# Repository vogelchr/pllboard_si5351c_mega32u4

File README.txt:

Si5351C PLL + ATmega32U4 PLL / OCXO-Control / Clock Generator

A PCB to provide a Si5351C clock generator IC with power via USB
and also have a ATmega32U4 control it.

The PLL chip can be provided two clocks:

 (1) standalone XTAL for Si5351C
      -> populate XT2

 (2a) external reference input (X8)
     (top right SMA connector when looking at top layer of PCB)

     -> Populate R18 (termination for SMA X8)
     -> Populate R27 (connects X8 with J3, Pin7)
     -> Populate R21, R22 (voltage divider to match Si5351C clkin voltage)

 (2b) quartz (TCXO, OCXO) oscillator connected to J3

     -> Populate R21, R22 (voltage divider to match Si5351C clkin voltage)
     -> A MCP47x6 DAC can be populated to provide a control voltage

If the clock (2a/2b) should be disciplined, this can be achieved
by having the ATmega32U4 determine the clock phase.

 (1) have a 1PPS input on the reference input (X8)

     -> Populate R17, R18 (termination, series resistor) for the
        atmega32u4 comparator input

     Then have the Si5351C output a suitable frequency to the atmega32u4
     on clock output 3, and...

     -> pouplate R25 to feed the external timer clock input T0,
        which has a maximum frequency of clkIO/2

          or

     -> populate R26, R20 and feed this frequency to the atmega32u4
        as the system clock. in this case, the otp memory of the
        Si5351C will have to be programmed so that it starts up
        with the clk3 active, and care must be taken not to turn
        off this clock, or the atmega32u4 will stop operating

     This way the ATmega32U4 can measure the clock phase of the 1PPS.

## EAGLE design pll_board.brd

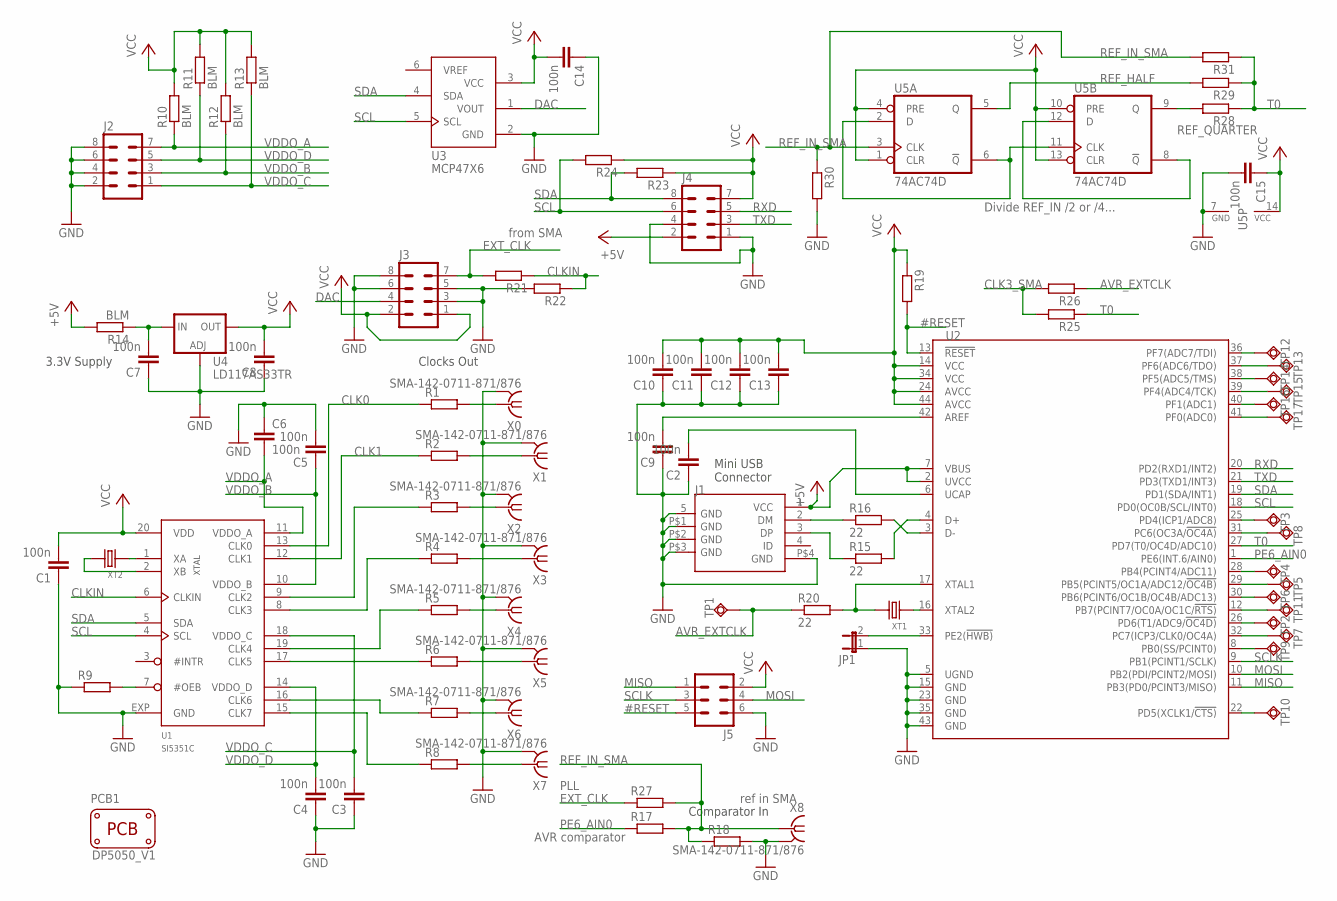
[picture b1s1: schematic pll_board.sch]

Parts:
C1, C2, C3, C4, C5, C6, C7, C8, C9, C10, C11, C12, C13, C14, C15: 100n; C0805
J1: MINI-USB-RCPT-B-5PS-R/A-SMD(ST-USB-002A); MINIUSB5+4P-SMD-0.8-90D
J2, J3, J4: MA04-2
J5: MA03-2
JP1: JP1E; JP1
PCB1: PCB_DP_SQUARE-5X5; DP5050_V1
R1, R2, R3, R4, R5, R6, R7, R8, R9, R17, R18, R19, R21, R22, R23, R24, R25, R26, R27, R28, R29, R30, R31: R-EU_R0805; R0805
R10, R11, R12, R13, R14: BLM; R0805
R15, R16, R20: 22; R0805
TP1, TP2, TP3, TP4, TP5, TP6, TP7, TP8, TP9, TP10, TP11, TP12, TP13, TP14, TP15, TP16, TP17: TPSQB1,27; B1,27
U1: SI5351C; QFN20
U2: MCU-ATMEGA32U4(TQFP44)-AU; TQFP44-0.8-9.6X9.6MM
U3: MCP47X6; SOT23-6
U4: LD117AS33TR; SOT223
U5: 74AC74D; SO14
X0, X1, X2, X3, X4, X5, X6, X7, X8: SMA-142-0711-871/876; J502-ND-142-0711-871/876
XT1, XT2: CRYSTAL'3225'; X4-SMD-3.2X2.5X0.7MM

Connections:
#OEB: R9.2, U1.7 (#OEB)
#RESET: J5.5, R19.2, U2.13 (!RESET)
+5V: J1.1 (VCC), J4.2, R14.2, U2.2 (UVCC), U2.7 (VBUS)
AREF: C9.2, U2.42 (AREF)
AVR_EXTCLK: R20.1, R26.1, TP1.TP
CLK0: R1.1, U1.13 (CLK0)
CLK0_SMA: R1.2, X0.1
CLK1: R2.1, U1.12 (CLK1)
CLK1_SMA: R2.2, X1.1
CLK2: R3.1, U1.9 (CLK2)
CLK2_SMA: R3.2, X2.1
CLK3: R4.1, U1.8 (CLK3)
CLK3_SMA: R4.2, R25.2, R26.2, X3.1
CLK4: R5.1, U1.19 (CLK4)
CLK4_SMA: R5.2, X4.1
CLK5: R6.1, U1.17 (CLK5)
CLK5_SMA: R6.2, X5.1
CLK6: R7.1, U1.16 (CLK6)
CLK6_SMA: R7.2, X6.1
CLK7: R8.1, U1.15 (CLK7)
CLK7_SMA: R8.2, X7.1
CLKIN: R21.1, R22.1, U1.6 (CLKIN)
DAC: J3.4, U3.1 (VOUT)
EXT_CLK: J3.7, R21.2, R27.1
GND: C1.1, C2.1, C3.1, C4.1, C5.2, C6.1, C7.1, C8.1, C9.1, C10.1, C11.1, C12.1, C13.1, C14.1, C15.2, J1.5 (GND), J1.P$1 (GND), J1.P$2 (GND), J1.P$3 (GND), J1.P$4 (GND), J2.2, J2.4, J2.6, J2.8, J3.3, J3.5, J3.6, J3.8, J4.1, J4.4, J5.6, JP1.1, R9.1, R18.2, R22.2, R30.2, U1.EXP (GND), U2.5 (UGND), U2.15 (GND), U2.23 (GND), U2.35 (GND), U2.43 (GND), U3.2 (GND), U4.1 (ADJ), U5.7 (GND), X0.G@1 (2), X0.G@2 (2), X0.G@3 (2), X0.G@4 (2), X1.G@1 (2), X1.G@2 (2), X1.G@3 (2), X1.G@4 (2), X2.G@1 (2), X2.G@2 (2), X2.G@3 (2), X2.G@4 (2), X3.G@1 (2), X3.G@2 (2), X3.G@3 (2), X3.G@4 (2), X4.G@1 (2), X4.G@2 (2), X4.G@3 (2), X4.G@4 (2), X5.G@1 (2), X5.G@2 (2), X5.G@3 (2), X5.G@4 (2), X6.G@1 (2), X6.G@2 (2), X6.G@3 (2), X6.G@4 (2), X7.G@1 (2), X7.G@2 (2), X7.G@3 (2), X7.G@4 (2), X8.G@1 (2), X8.G@2 (2), X8.G@3 (2), X8.G@4 (2)
LDO_IN: C7.2, R14.1, U4.3 (IN)
MISO: J5.1, U2.11 (PB3(PD0/PCINT3/MISO))
MOSI: J5.4, U2.10 (PB2(PDI/PCINT2/MOSI))
unnamed: U2.16 (XTAL2), XT1.2 (1)
unnamed: U1.1 (XA), XT2.2 (1)
unnamed: R20.2, U2.17 (XTAL1), XT1.4 (2)
unnamed: JP1.2, U2.33 (PE2(!HWB))
unnamed: U1.2 (XB), XT2.4 (2)
P8: TP9.TP, U2.8 (PB0(SS/PCINT0))
P12: TP11.TP, U2.12 (PB7(PCINT7/OC0A/OC1C/!RTS))
P22: TP10.TP, U2.22 (PD5(XCLK1/!CTS))
P25: TP3.TP, U2.25 (PD4(ICP1/ADC8))
P26: TP2.TP, U2.26 (PD6(T1/ADC9/!OC4D))
P28: TP4.TP, U2.28 (PB4(PCINT4/ADC11))
P29: TP5.TP, U2.29 (PB5(PCINT5/OC1A/ADC12/!OC4B))
P30: TP6.TP, U2.30 (PB6(PCINT6/OC1B/OC4B/ADC13))
P31: TP8.TP, U2.31 (PC6(OC3A/!OC4A))
P32: TP7.TP, U2.32 (PC7(ICP3/CLK0/OC4A))
P36: TP12.TP, U2.36 (PF7(ADC7/TDI))
P37: TP13.TP, U2.37 (PF6(ADC6/TDO))
P38: TP14.TP, U2.38 (PF5(ADC5/TMS))
P39: TP15.TP, U2.39 (PF4(ADC4/TCK))
P40: TP16.TP, U2.40 (PF1(ADC1))
P41: TP17.TP, U2.41 (PF0(ADC0))
PE6_AIN0: R17.1, U2.1 (PE6(INT.6/AIN0))
REF_HALF: R29.2, U5.5 (Q)
REF_HALF_N: U5.2 (D), U5.6 (!Q), U5.11 (CLK)
REF_IN_SMA: R17.2, R18.1, R27.2, R30.1, R31.2, U5.3 (CLK), X8.1
REF_QUARTER: R28.2, U5.9 (Q)
REF_QUARTER_N: U5.8 (!Q), U5.12 (D)
RXD: J4.5, U2.20 (PD2(RXD1/INT2))
SCL: J4.6, R24.2, U1.4 (SCL), U2.18 (PD0(OC0B/SCL/INT0)), U3.5 (SCL)
SCLK: J5.3, U2.9 (PB1(PCINT1/SCLK))
SDA: J4.8, R23.2, U1.5 (SDA), U2.19 (PD1(SDA/INT1)), U3.4 (SDA)
T0: R25.1, R28.1, R29.1, R31.1, U2.27 (PD7(T0/OC4D/ADC10))
TXD: J4.3, U2.21 (PD3(TXD1/INT3))
UCAP: C2.2, U2.6 (UCAP)
USBD_CON_N: J1.2 (DM), R16.1
USBD_CON_P: J1.3 (DP), R15.1
USBD_N: R16.2, U2.3 (D-)
USBD_P: R15.2, U2.4 (D+)
VCC: C1.2, C8.2, C10.2, C11.2, C12.2, C13.2, C14.2, C15.1, J3.1, J3.2, J4.7, J5.2, R10.2, R11.2, R12.2, R13.2, R19.1, R23.1, R24.1, U1.20 (VDD), U2.14 (VCC), U2.24 (AVCC), U2.34 (VCC), U2.44 (AVCC), U3.3 (VCC), U4.4 (OUT), U5.1 (CLR), U5.4 (PRE), U5.10 (PRE), U5.13 (CLR), U5.14 (VCC)
VDDO_A: C6.2, J2.7, R10.1, U1.11 (VDDO_A)
VDDO_B: C5.1, J2.3, R12.1, U1.10 (VDDO_B)
VDDO_C: C3.2, J2.1, R13.1, U1.18 (VDDO_C)
VDDO_D: C4.2, J2.5, R11.1, U1.14 (VDDO_D)

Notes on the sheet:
Comparator In
Clocks Out
3.3V Supply
Mini USB Connector
from SMA
ref in SMA
AVR comparator
PLL
Divide REF_IN /2 or /4...

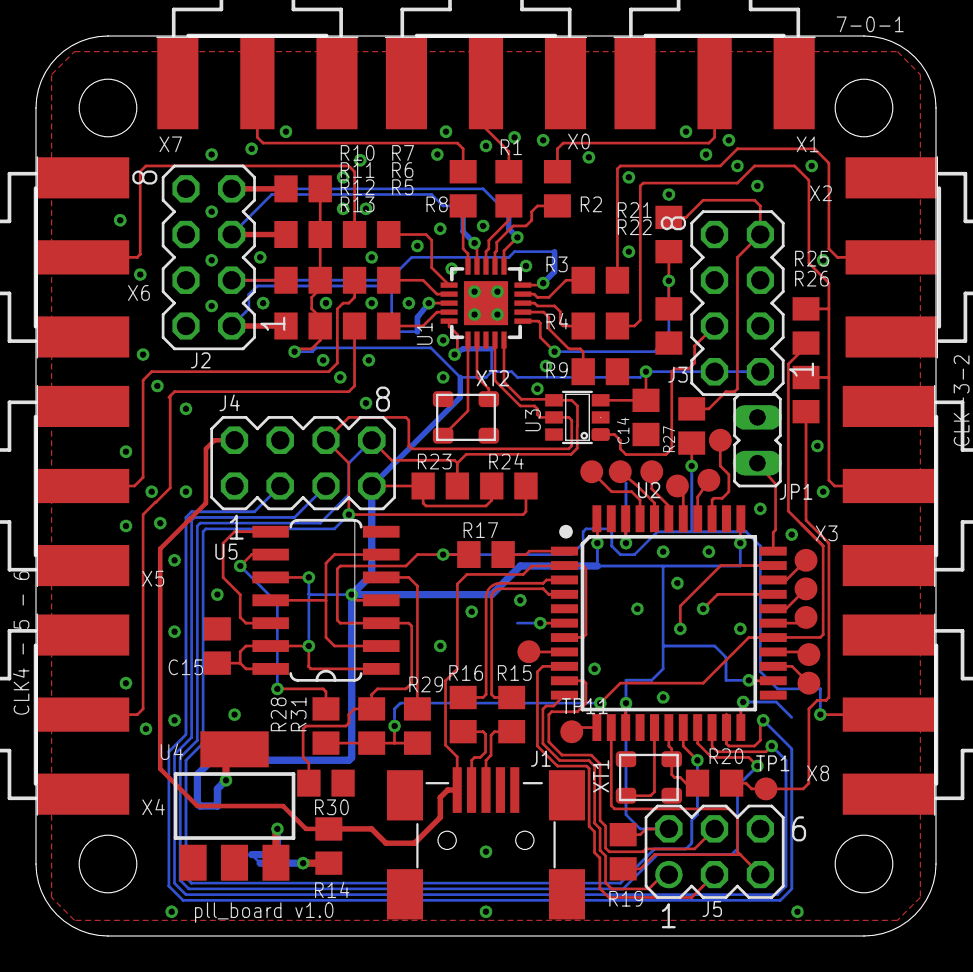
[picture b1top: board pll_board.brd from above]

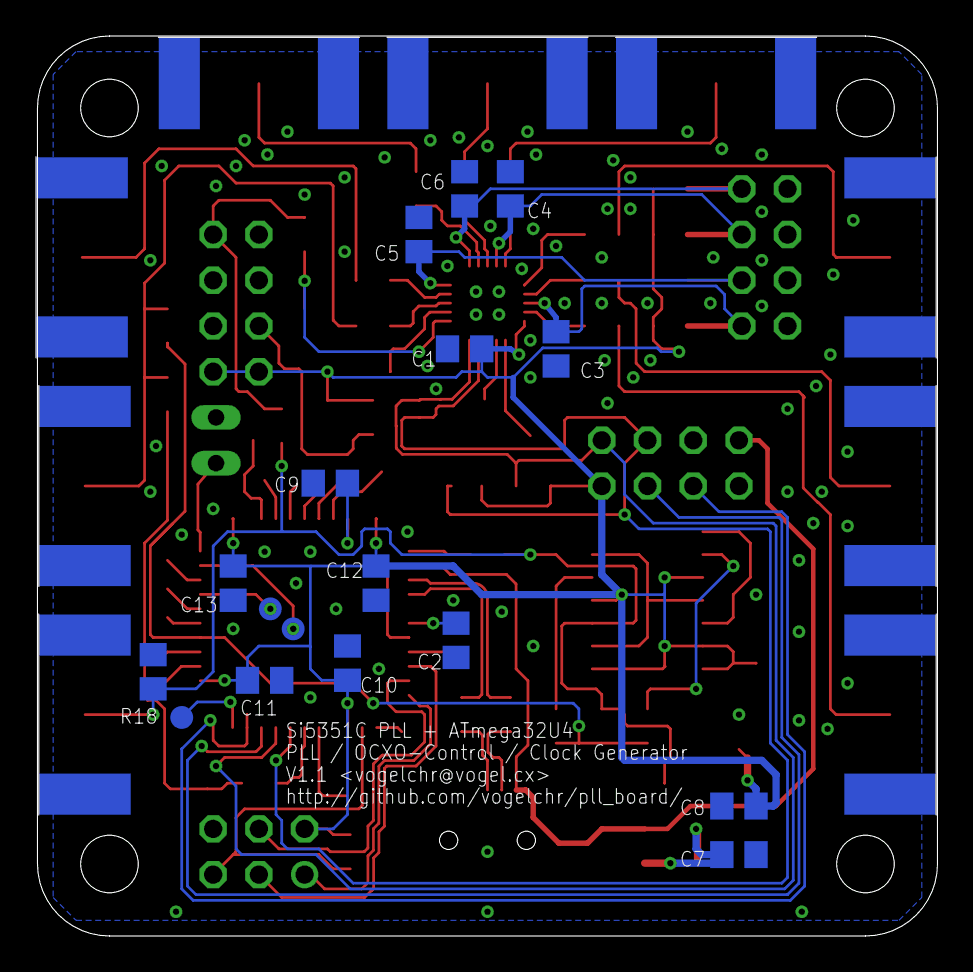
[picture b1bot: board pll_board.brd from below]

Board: 2 copper layers, 50.0 x 50.0 mm, 86 parts (17 on the bottom side), 71 nets.

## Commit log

2017-08-26 Initially empty repo.
2017-08-26 Initial version.
2017-08-26 Added PDF of schematics.
2017-08-26 .gitignore
2017-08-26 Add USB +5V on i2c/uart connector.
2017-08-26 Added README.
2017-12-24 First start of Firmware, using my old am2302 as an example.
2017-12-25 More work.
2017-12-25 more work
2017-12-25 Change from unpacked lufa .zip to git submodules.
2018-01-10 Add firmware build artifacts to .gitignore.
